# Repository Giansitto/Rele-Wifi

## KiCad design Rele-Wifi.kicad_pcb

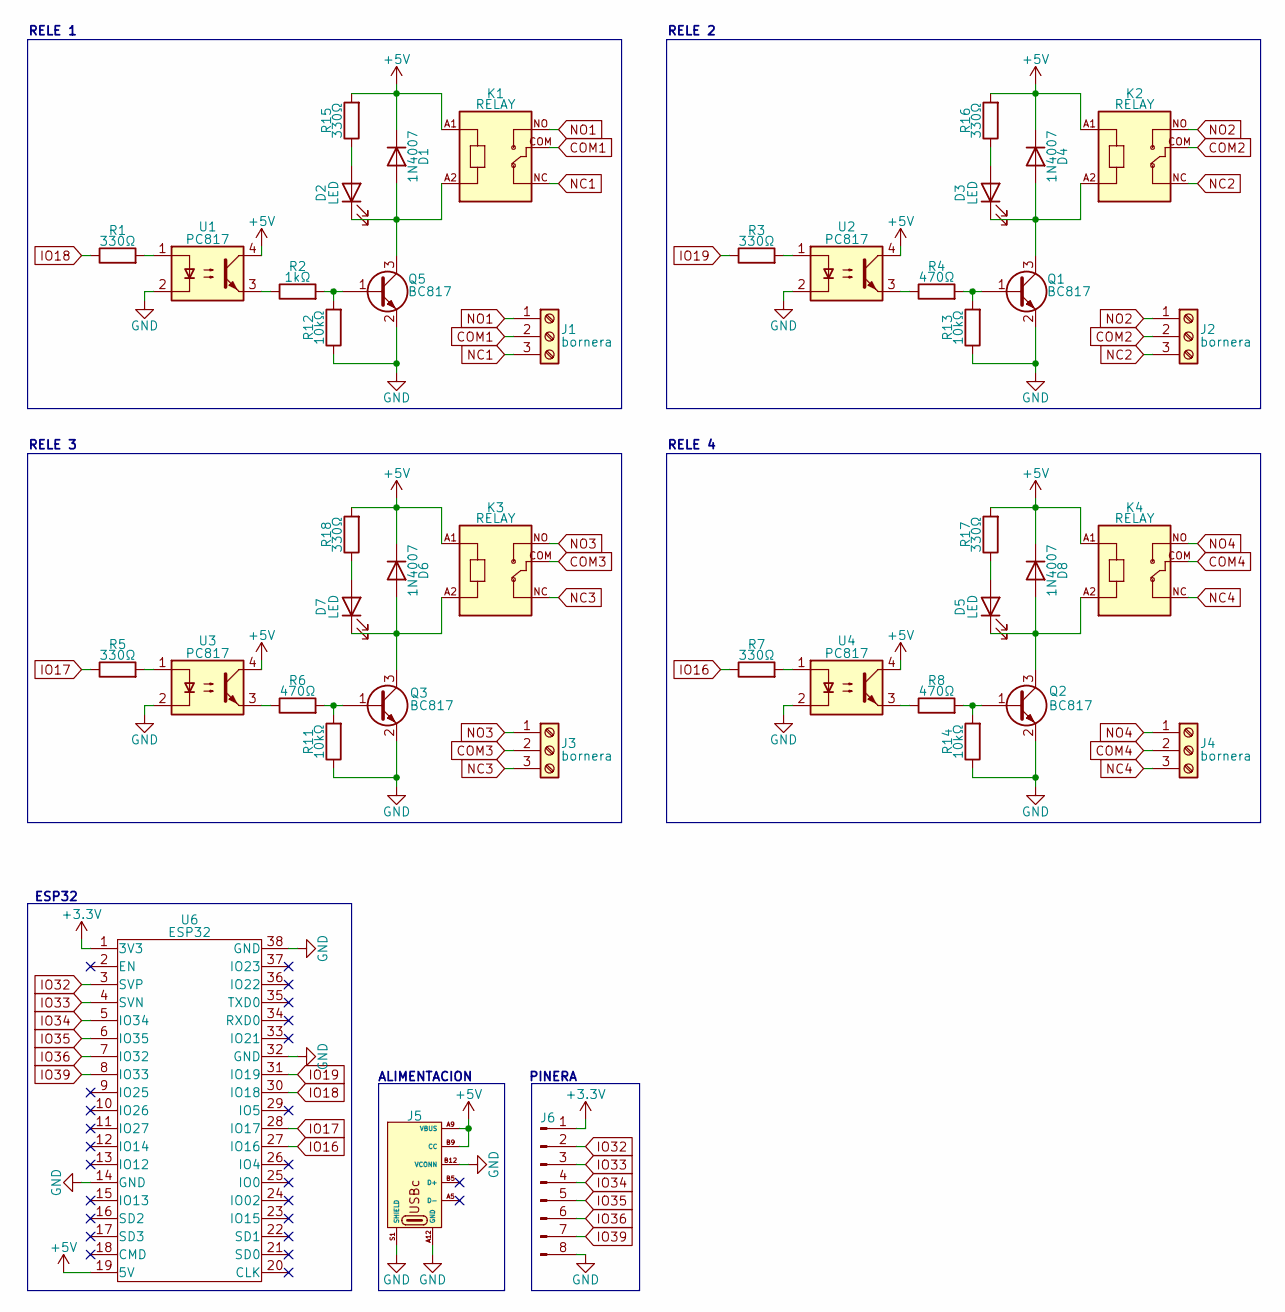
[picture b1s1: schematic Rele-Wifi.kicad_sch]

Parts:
D1, D4, D6, D8: 1N4007; D_SMA
D2, D3, D5, D7: LED; LED_D3.0mm
J1, J2, J3, J4: bornera; TerminalBlock_bornier-3_P5.08mm
J5: USB_C_Receptacle_GCT_USB4135-GF-A_6P_TopMnt_Horizontal
J6: Conn_01x08_Pin; PinHeader_1x08_P2.54mm_Vertical
K1, K2, K3, K4: RELAY; RELAY_SRD-05VDC-SL-C
Q1, Q2, Q3, Q5: BC817; SOT-23
R1, R3, R5, R7, R15, R16, R17, R18: 330Ω; R_0805_2012Metric
R2: 1kΩ; R_0805_2012Metric
R4, R6, R8: 470Ω; R_0805_2012Metric
R11, R12, R13, R14: 10kΩ; R_0805_2012Metric
U1, U2, U3, U4: PC817; SSO-4_6.7x5.1mm_P2.54mm_Clearance8mm
U6: ESP32; ESP32S

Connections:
+3.3V: J6.1, U6.1 (3V3)
+5V: D1.1 (K), D4.1 (K), D6.1 (K), D8.1 (K), J5.A9 (VBUS), J5.B9 (CC), K1.A1, K2.A1, K3.A1, K4.A1, R15.2, R16.2, R17.2, R18.2, U1.4, U2.4, U3.4, U4.4, U6.19 (5V)
COM1: J1.2, K1.COM
COM2: J2.2, K2.COM
COM3: J3.2, K3.COM
COM4: J4.2, K4.COM
GND: J5.A12 (GND), J5.B12 (VCONN), J5.S1 (SHIELD), J6.8, Q1.2 (E), Q2.2 (E), Q3.2 (E), Q5.2 (E), R11.1, R12.1, R13.1, R14.1, U1.2, U2.2, U3.2, U4.2, U6.14 (GND), U6.32 (GND), U6.38 (GND)
IO16: R7.1, U6.27 (IO16)
IO17: R5.1, U6.28 (IO17)
IO18: R1.1, U6.30 (IO18)
IO19: R3.1, U6.31 (IO19)
IO32: J6.2, U6.3 (SVP)
IO33: J6.3, U6.4 (SVN)
IO34: J6.4, U6.5 (IO34)
IO35: J6.5, U6.6 (IO35)
IO36: J6.6, U6.7 (IO32)
IO39: J6.7, U6.8 (IO33)
NC1: J1.3, K1.NC
NC2: J2.3, K2.NC
NC3: J3.3, K3.NC
NC4: J4.3, K4.NC
NO1: J1.1, K1.NO
NO2: J2.1, K2.NO
NO3: J3.1, K3.NO
NO4: J4.1, K4.NO
unnamed: D1.2 (A), D2.1 (K), K1.A2, Q5.3 (C)
unnamed: D2.2 (A), R15.1
unnamed: D3.2 (A), R16.1
unnamed: D3.1 (K), D4.2 (A), K2.A2, Q1.3 (C)
unnamed: D5.2 (A), R17.1
unnamed: D5.1 (K), D8.2 (A), K4.A2, Q2.3 (C)
unnamed: D6.2 (A), D7.1 (K), K3.A2, Q3.3 (C)
unnamed: D7.2 (A), R18.1
unnamed: Q1.1 (B), R4.2, R13.2
unnamed: Q2.1 (B), R8.2, R14.2
unnamed: Q3.1 (B), R6.2, R11.2
unnamed: Q5.1 (B), R2.2, R12.2
unnamed: R1.2, U1.1
unnamed: R2.1, U1.3
unnamed: R3.2, U2.1
unnamed: R4.1, U2.3
unnamed: R5.2, U3.1
unnamed: R6.1, U3.3
unnamed: R7.2, U4.1
unnamed: R8.1, U4.3

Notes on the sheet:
ESP32
RELE 2
PINERA
RELE 4
RELE 3
RELE 1
ALIMENTACION

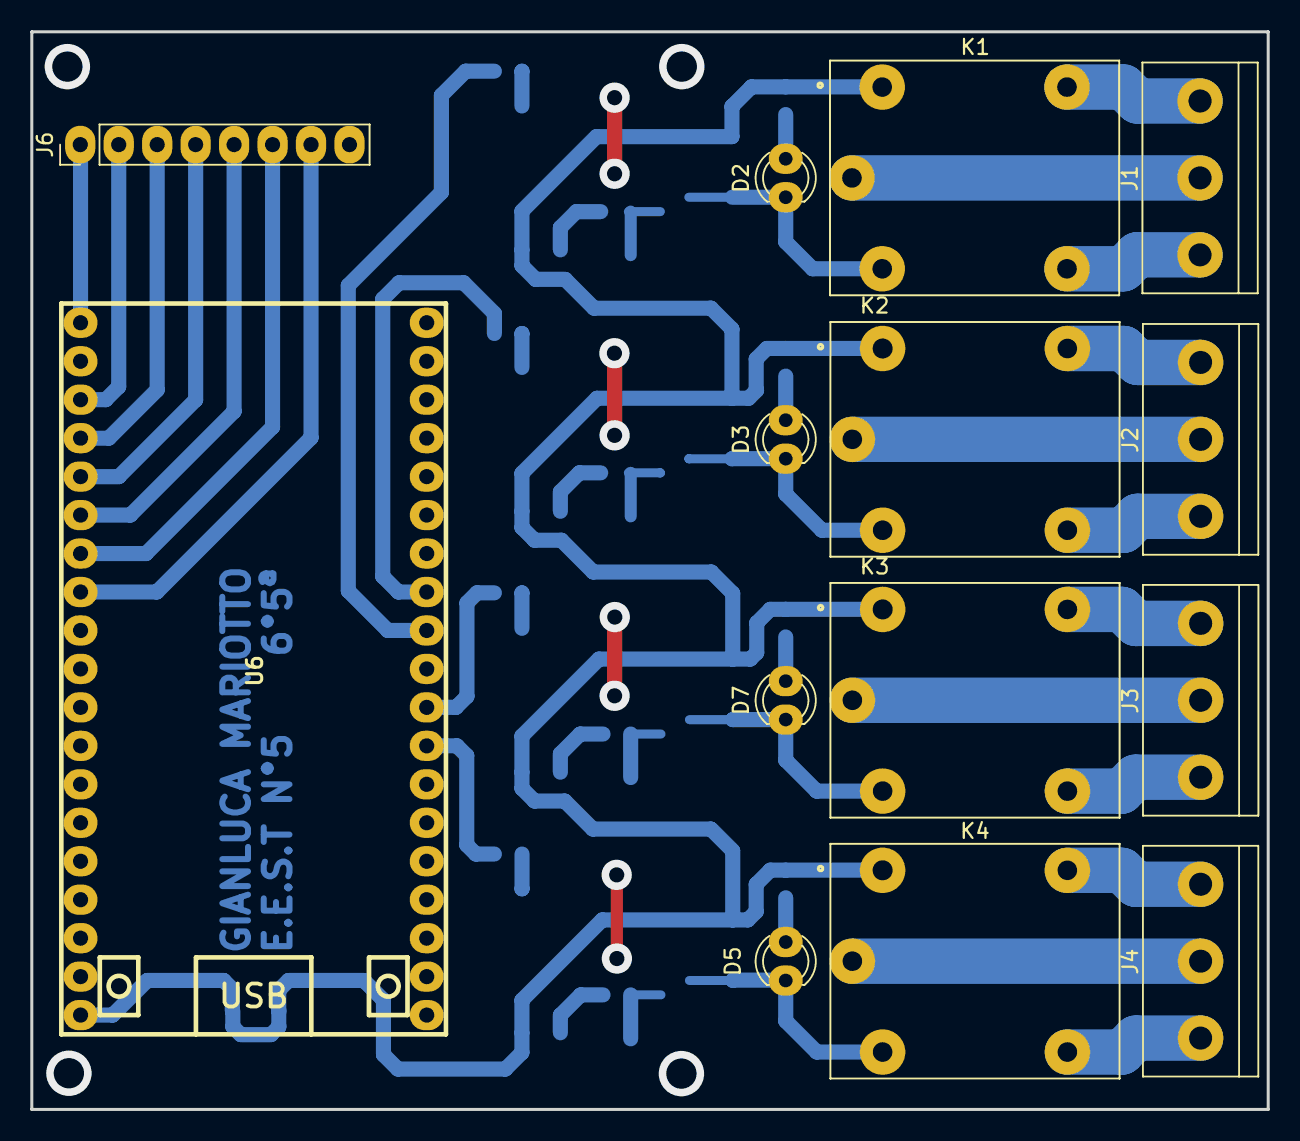
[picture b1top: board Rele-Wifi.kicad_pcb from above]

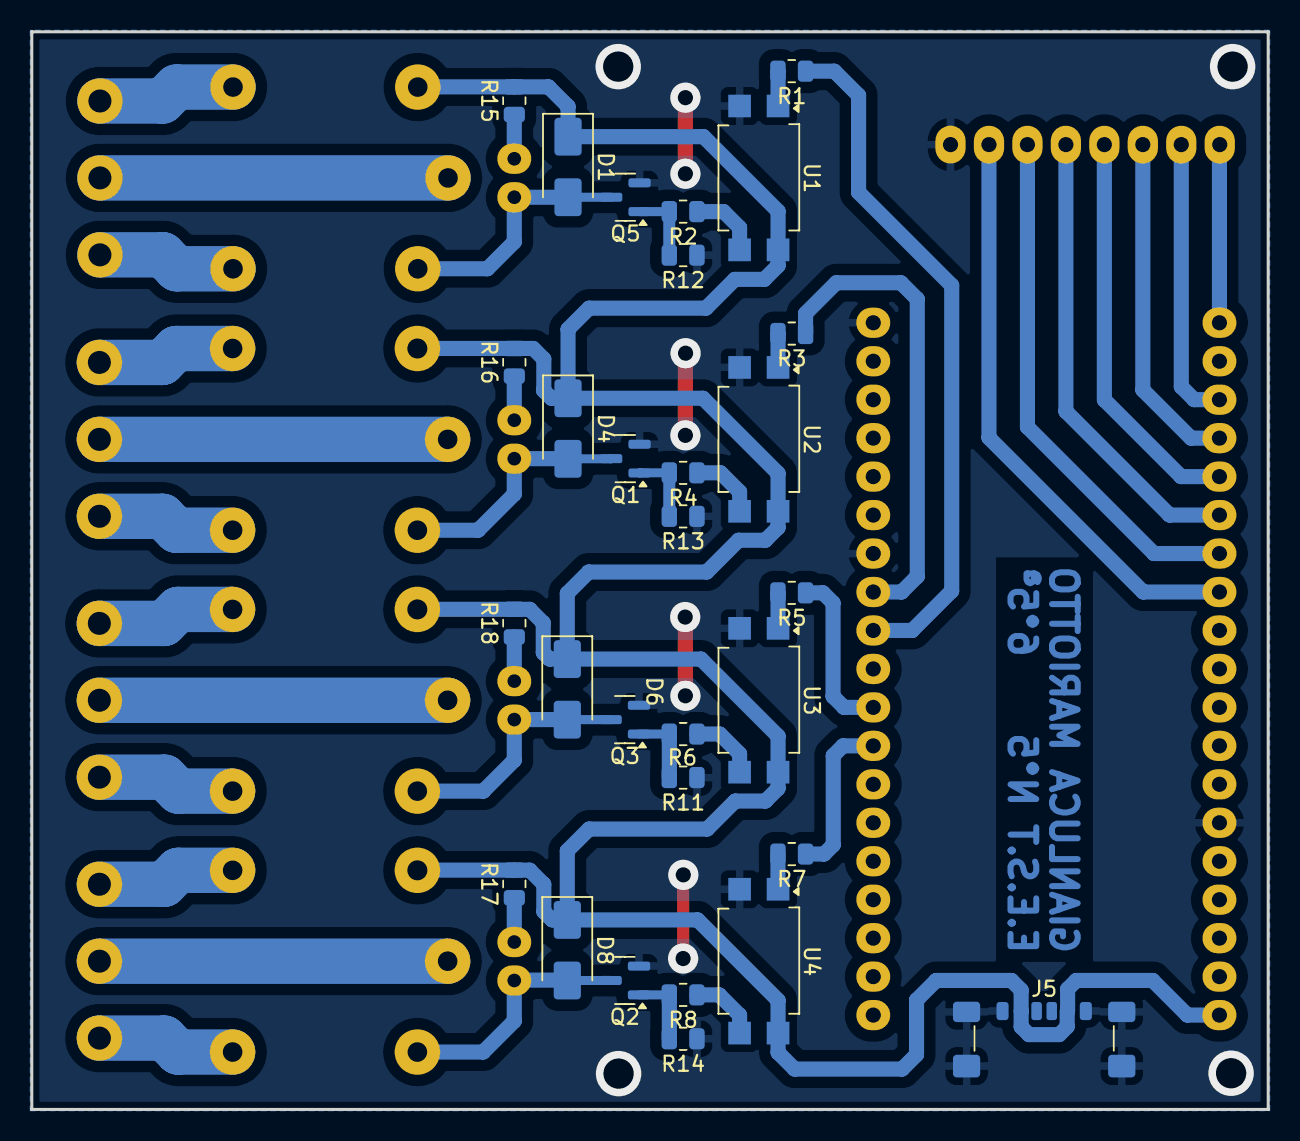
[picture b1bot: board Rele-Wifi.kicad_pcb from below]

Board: 2 copper layers, 81.7 x 71.2 mm, 43 parts (29 on the bottom side), 45 nets.

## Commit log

2025-05-25 primer commit
2025-05-25 Agregué la carpeta de hardware con los archivos de KiCad
2025-05-25 Borré la carpeta hardware porque estaba mal
2025-05-25 Agregué el proyecto KiCad en la carpeta hardware
2025-06-05 kicad del Rele-Wifi terminado
